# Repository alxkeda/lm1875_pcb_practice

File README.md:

# lm1875_pcb_practice

First PCB, designed May 2025. My GitHub is pretty empty right now besides my Zotbins contributions so I thought I'd start adding all my projects here! More to come soon.

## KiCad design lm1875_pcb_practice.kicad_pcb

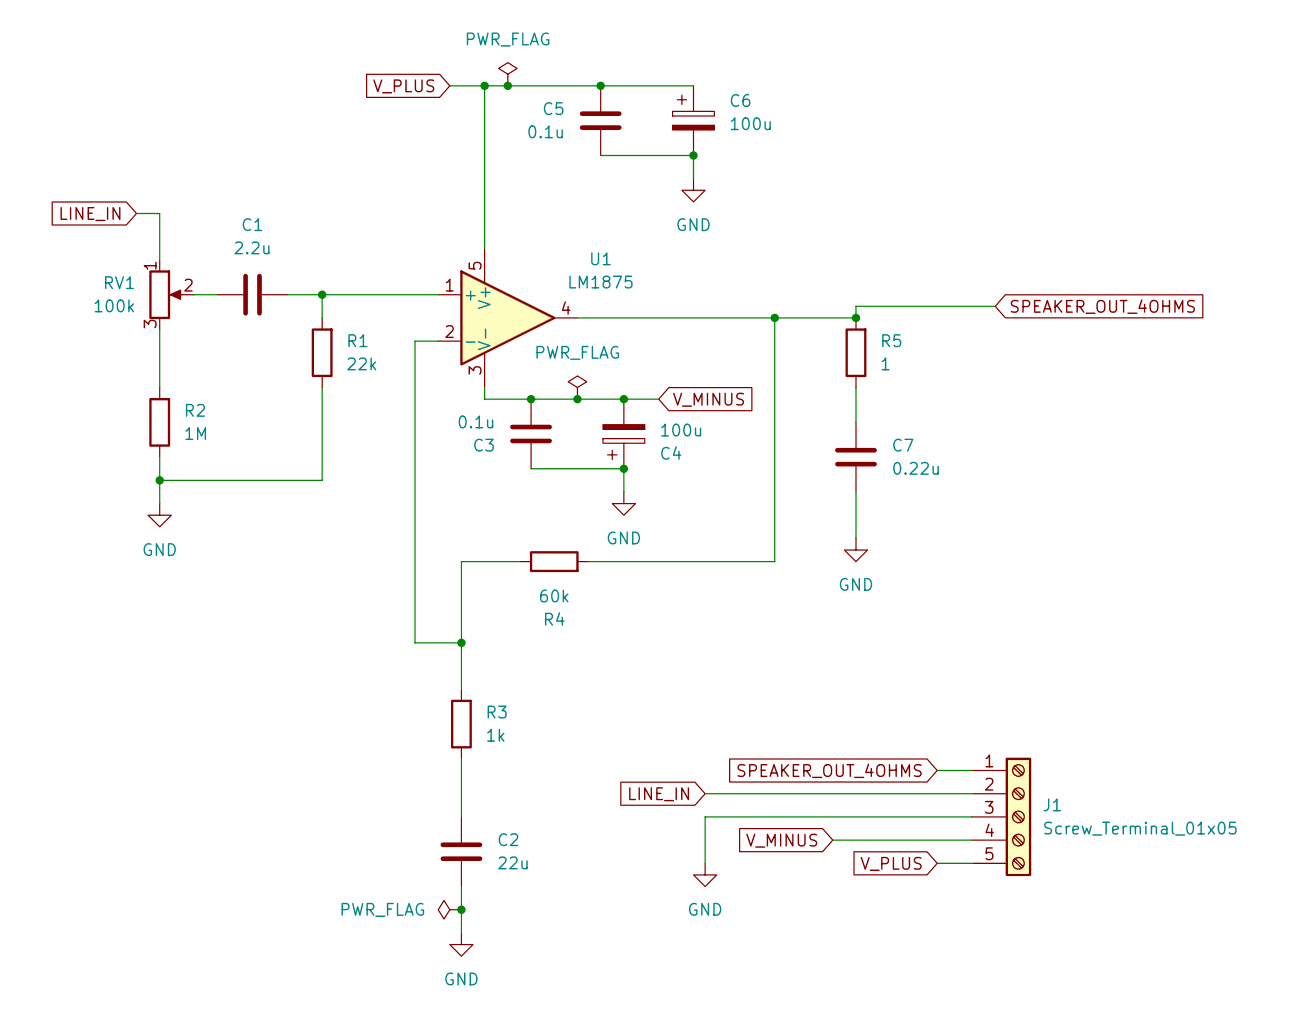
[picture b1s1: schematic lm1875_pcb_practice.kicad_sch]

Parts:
C1: 2.2u; C_0603_1608Metric
C2: 22u; C_0603_1608Metric
C3, C5: 0.1u; C_0603_1608Metric
C4, C6: 100u; CP_Elec_6.3x4.9
C7: 0.22u; C_0603_1608Metric
J1: Screw_Terminal_01x05; TerminalBlock_Phoenix_MKDS-1,5-5_1x05_P5.00mm_Horizontal
R1: 22k; R_0603_1608Metric
R2: 1M; R_0603_1608Metric
R3: 1k; R_0603_1608Metric
R4: 60k; R_0603_1608Metric
R5: 1; R_0805_2012Metric_Pad1.20x1.40mm_HandSolder
RV1: 100k; Potentiometer_Bourns_PTV09A-1_Single_Vertical
U1: LM1875; TO-220-5_P3.4x3.7mm_StaggerOdd_Lead3.8mm_Vertical

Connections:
GND: C2.2, C3.1, C4.1, C5.2, C6.2, C7.2, J1.3, R1.1, R2.1
LINE_IN: J1.2, RV1.1
unnamed: C1.1, RV1.2
unnamed: C2.1, R3.1
unnamed: C7.1, R5.1
unnamed: R2.2, RV1.3
unnamed: C1.2, R1.2, U1.1 (+)
unnamed: R3.2, R4.1, U1.2 (-)
SPEAKER_OUT_4OHMS: J1.1, R4.2, R5.2, U1.4
V_MINUS: C3.2, C4.2, J1.4, U1.3 (V-)
V_PLUS: C5.1, C6.1, J1.5, U1.5 (V+)

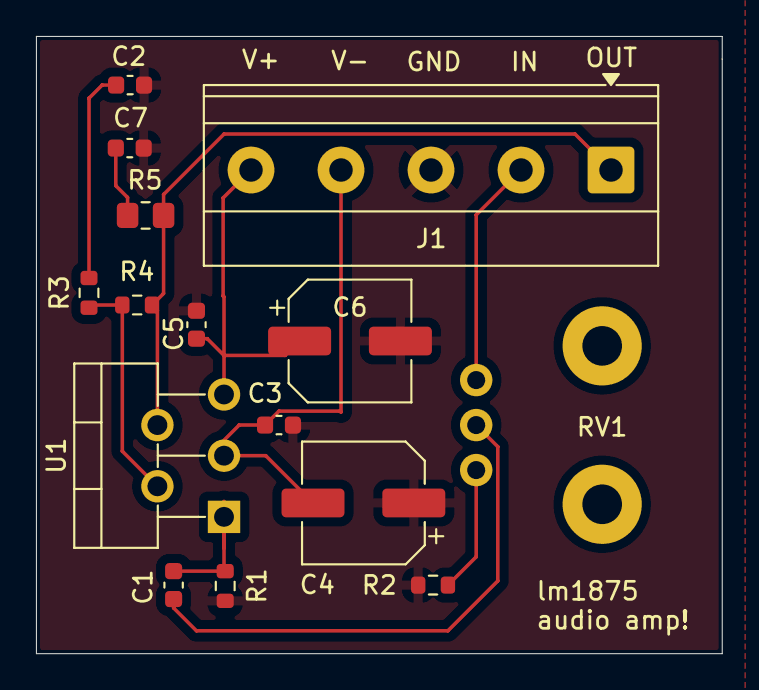
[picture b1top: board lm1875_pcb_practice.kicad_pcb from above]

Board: 2 copper layers, 38.1 x 34.3 mm, 15 parts (1 on the bottom side), 11 nets.

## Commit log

2025-09-28 init
